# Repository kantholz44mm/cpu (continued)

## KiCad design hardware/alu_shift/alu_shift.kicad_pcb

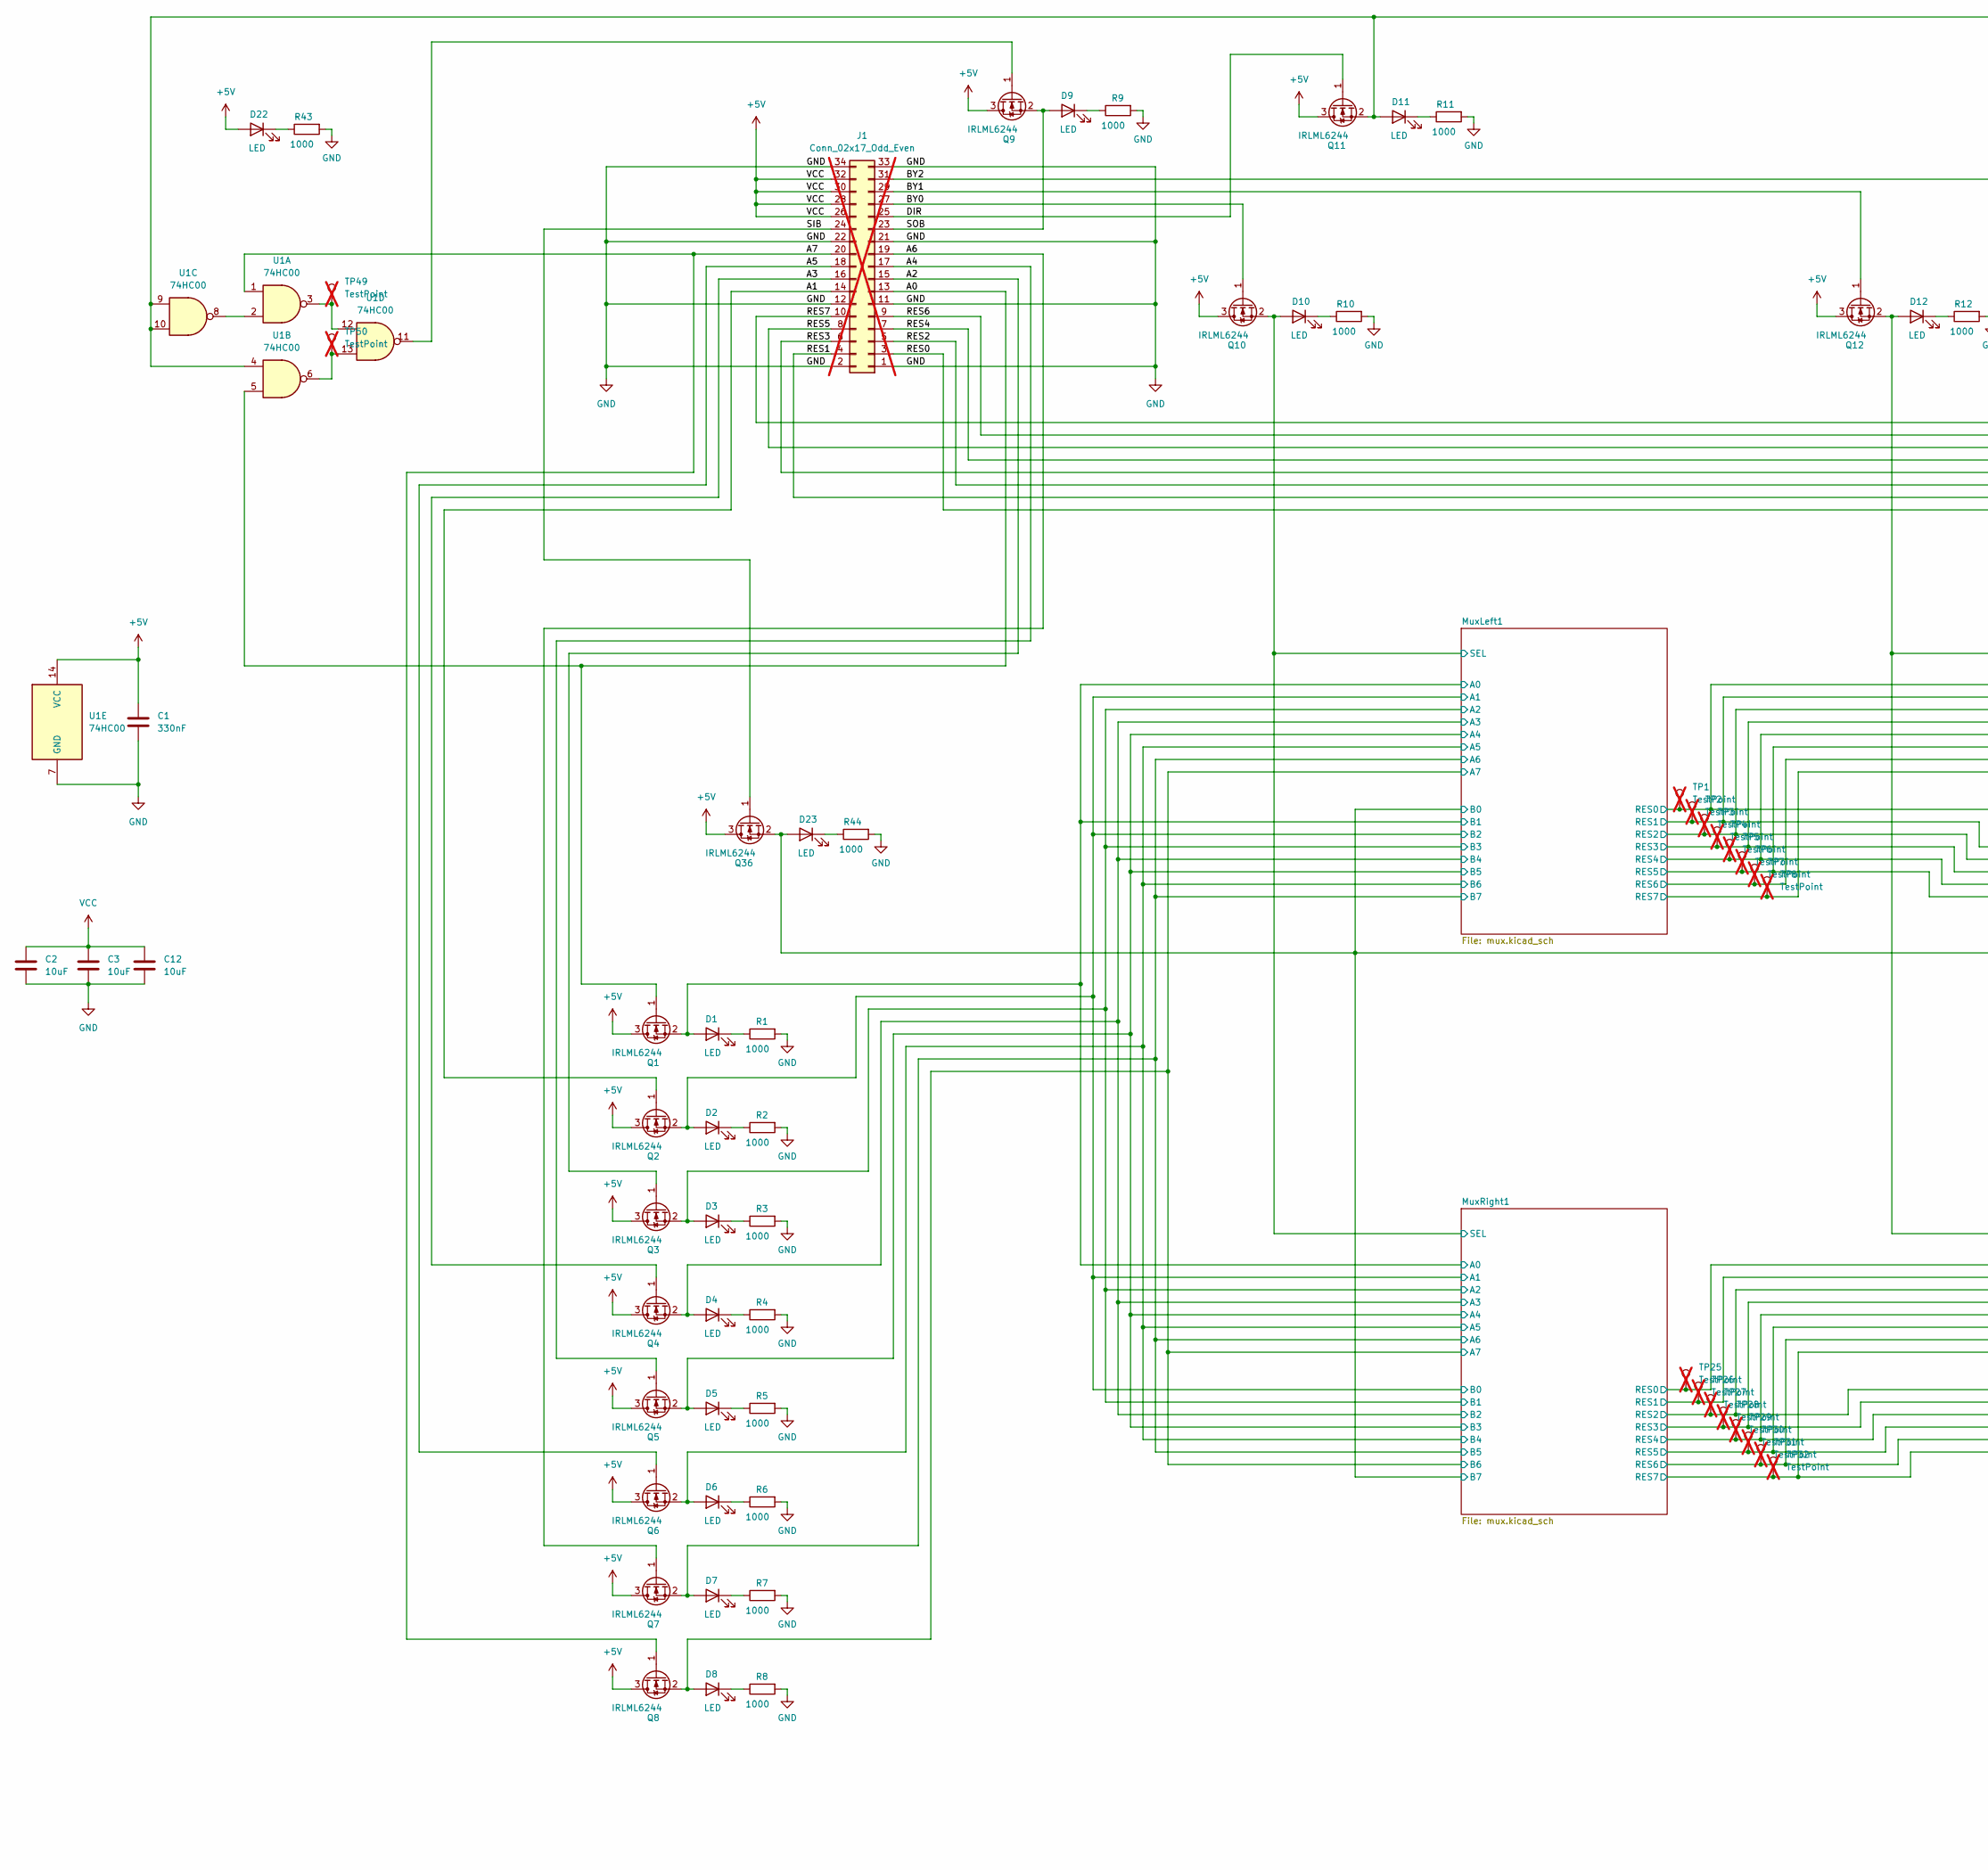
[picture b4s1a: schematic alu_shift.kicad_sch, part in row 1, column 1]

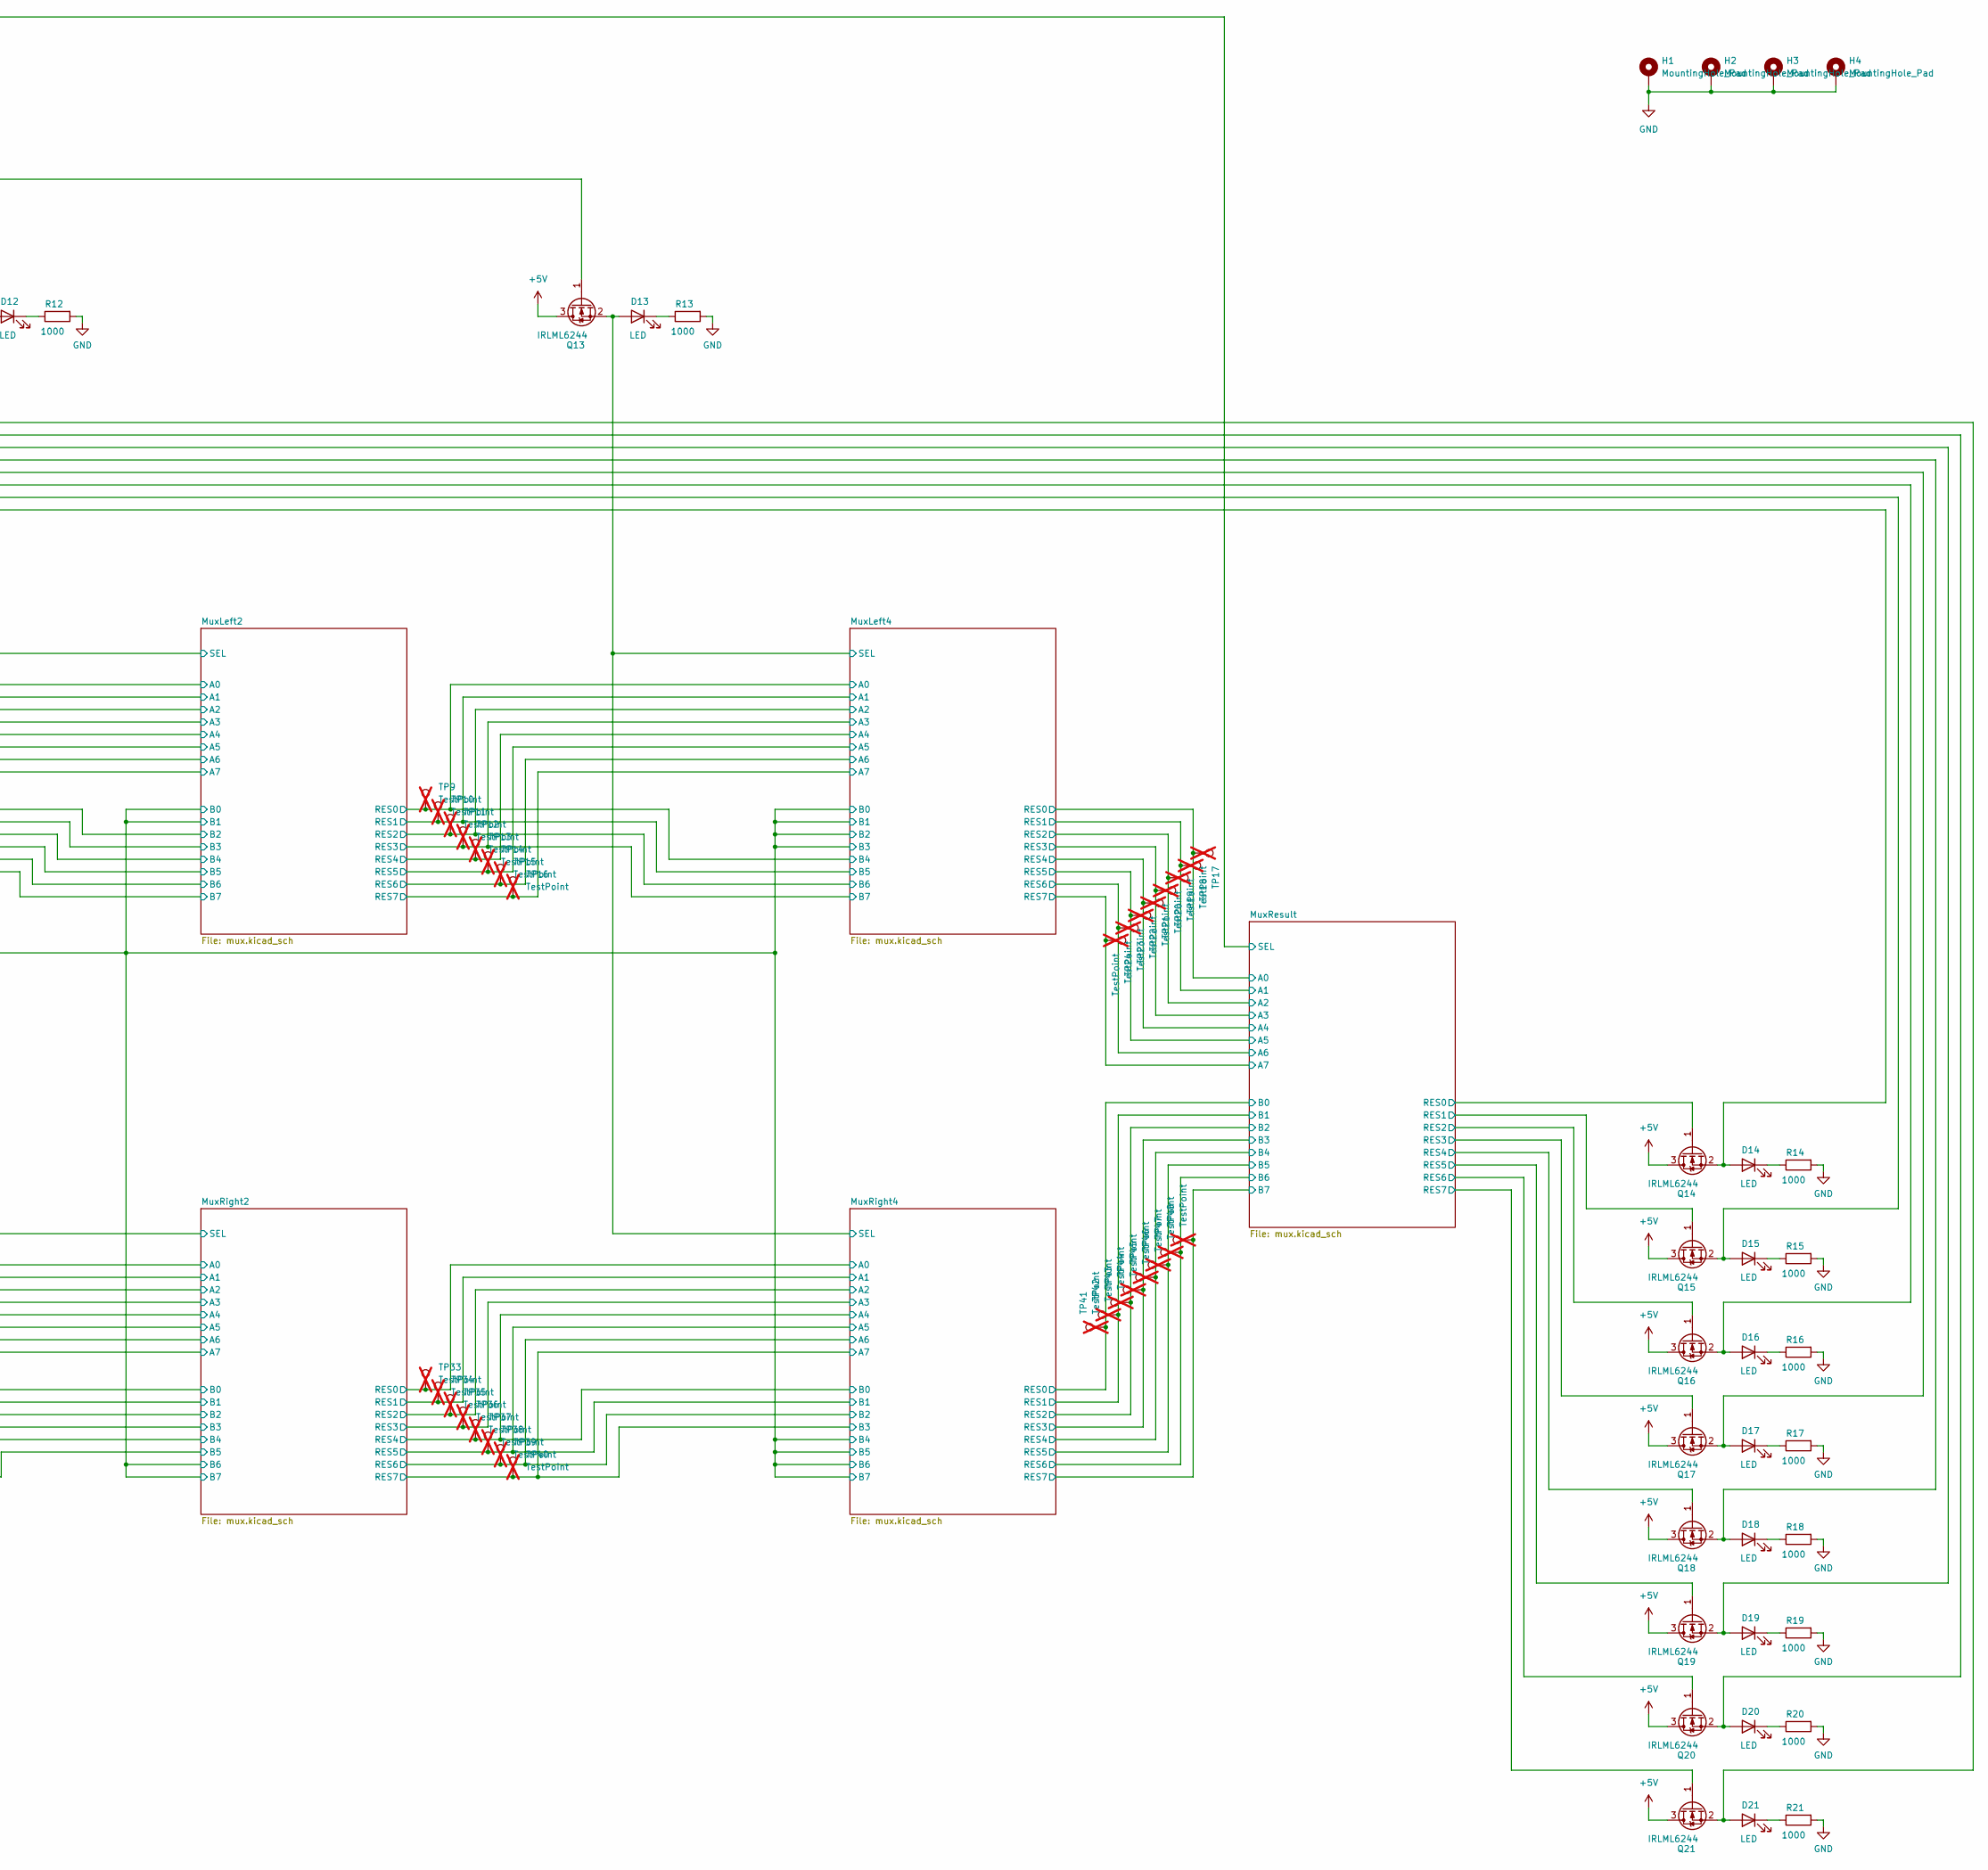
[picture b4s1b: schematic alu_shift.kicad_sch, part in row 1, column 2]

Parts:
C1: 330nF; C_0603_1608Metric_Pad1.08x0.95mm_HandSolder; LCSC C2918485
C2, C3, C12: 10uF; C_0603_1608Metric_Pad1.08x0.95mm_HandSolder; LCSC C2909630
D1, D2, D3, D4, D5, D6, D7, D8, D9, D10, D11, D12, D13, D14, D15, D16, D17, D18, D19, D20, D21, D22, D23: LED; LED_0603_1608Metric_Pad1.05x0.95mm_HandSolder; LCSC C84267
H1, H2, H3, H4: MountingHole_Pad; MountingHole_2.2mm_M2_Pad
J1: Conn_02x17_Odd_Even; PinHeader_2x17_P2.54mm_Horizontal; not fitted
Q1, Q2, Q3, Q4, Q5, Q6, Q7, Q8, Q9, Q10, Q11, Q12, Q13, Q14, Q15, Q16, Q17, Q18, Q19, Q20, Q21, Q36: IRLML6244; SOT-23-3; LCSC C5123965
R1, R2, R3, R4, R5, R6, R7, R8, R9, R10, R11, R12, R13, R14, R15, R16, R17, R18, R19, R20, R21, R43, R44: 1000; R_0603_1608Metric_Pad0.98x0.95mm_HandSolder; LCSC C21190
TP1, TP2, TP3, TP4, TP5, TP6, TP7, TP8, TP9, TP10, TP11, TP12, TP13, TP14, TP15, TP16, TP17, TP18, TP19, TP20, TP21, TP22, TP23, TP24, TP25, TP26, TP27, TP28, TP29, TP30, TP31, TP32, TP33, TP34, TP35, TP36, TP37, TP38, TP39, TP40, TP41, TP42, TP43, TP44, TP45, TP46, TP47, TP48, TP49, TP50: TestPoint; TestPoint_Pad_D2.0mm; not fitted
U1: 74HC00; SOIC-14_3.9x8.7mm_P1.27mm; LCSC C5586

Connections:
+5V: C1.1, C2.1, C3.1, C12.1, D22.2 (A), J1.26, J1.28, J1.30, J1.32, Q1.3 (D), Q2.3 (D), Q3.3 (D), Q4.3 (D), Q5.3 (D), Q6.3 (D), Q7.3 (D), Q8.3 (D), Q9.3 (D), Q10.3 (D), Q11.3 (D), Q12.3 (D), Q13.3 (D), Q14.3 (D), Q15.3 (D), Q16.3 (D), Q17.3 (D), Q18.3 (D), Q19.3 (D), Q20.3 (D), Q21.3 (D), Q36.3 (D), U1.14 (VCC); also elsewhere on the board
/A0: J1.13, Q1.1 (G), U1.5
/A1: J1.14, Q2.1 (G)
/A2: J1.15, Q3.1 (G)
/A3: J1.16, Q4.1 (G)
/A4: J1.17, Q5.1 (G)
/A5: J1.18, Q6.1 (G)
/A6: J1.19, Q7.1 (G)
/A7: J1.20, Q8.1 (G), U1.1
/BY0: J1.27, Q10.1 (G)
/BY1: J1.29, Q12.1 (G)
/BY2: J1.31, Q13.1 (G)
/DIR: J1.25, Q11.1 (G)
/MuxLeft1/A0: D1.2 (A), Q1.2 (S); also elsewhere on the board
/MuxLeft1/A1: D2.2 (A), Q2.2 (S); also elsewhere on the board
/MuxLeft1/A2: D3.2 (A), Q3.2 (S); also elsewhere on the board
/MuxLeft1/A3: D4.2 (A), Q4.2 (S); also elsewhere on the board
/MuxLeft1/A4: D5.2 (A), Q5.2 (S); also elsewhere on the board
/MuxLeft1/A5: D6.2 (A), Q6.2 (S); also elsewhere on the board
/MuxLeft1/A6: D7.2 (A), Q7.2 (S); also elsewhere on the board
/MuxLeft1/A7: D8.2 (A), Q8.2 (S); also elsewhere on the board
/MuxLeft1/B0: D23.2 (A), Q36.2 (S); also elsewhere on the board
/MuxLeft1/RES0: TP1.1; also elsewhere on the board
/MuxLeft1/RES1: TP2.1; also elsewhere on the board
/MuxLeft1/RES2: TP3.1; also elsewhere on the board
/MuxLeft1/RES3: TP4.1; also elsewhere on the board
/MuxLeft1/RES4: TP5.1; also elsewhere on the board
/MuxLeft1/RES5: TP6.1; also elsewhere on the board
/MuxLeft1/RES6: TP7.1; also elsewhere on the board
/MuxLeft1/RES7: TP8.1; also elsewhere on the board
/MuxLeft1/SEL: D10.2 (A), Q10.2 (S); also elsewhere on the board
/MuxLeft2/RES0: TP9.1; also elsewhere on the board
/MuxLeft2/RES1: TP10.1; also elsewhere on the board
/MuxLeft2/RES2: TP11.1; also elsewhere on the board
/MuxLeft2/RES3: TP12.1; also elsewhere on the board
/MuxLeft2/RES4: TP13.1; also elsewhere on the board
/MuxLeft2/RES5: TP14.1; also elsewhere on the board
/MuxLeft2/RES6: TP15.1; also elsewhere on the board
/MuxLeft2/RES7: TP16.1; also elsewhere on the board
/MuxLeft2/SEL: D12.2 (A), Q12.2 (S); also elsewhere on the board
/MuxLeft4/RES0: TP17.1; also elsewhere on the board
/MuxLeft4/RES1: TP18.1; also elsewhere on the board
/MuxLeft4/RES2: TP19.1; also elsewhere on the board
/MuxLeft4/RES3: TP20.1; also elsewhere on the board
/MuxLeft4/RES4: TP21.1; also elsewhere on the board
/MuxLeft4/RES5: TP22.1; also elsewhere on the board
/MuxLeft4/RES6: TP23.1; also elsewhere on the board
/MuxLeft4/RES7: TP24.1; also elsewhere on the board
/MuxLeft4/SEL: D13.2 (A), Q13.2 (S); also elsewhere on the board
/MuxResult/B0: TP41.1; also elsewhere on the board
/MuxResult/B1: TP42.1; also elsewhere on the board
/MuxResult/B2: TP43.1; also elsewhere on the board
/MuxResult/B3: TP44.1; also elsewhere on the board
/MuxResult/B4: TP45.1; also elsewhere on the board
/MuxResult/B5: TP46.1; also elsewhere on the board
/MuxResult/B6: TP47.1; also elsewhere on the board
/MuxResult/B7: TP48.1; also elsewhere on the board
/MuxResult/RES0: Q14.1 (G); also elsewhere on the board
/MuxResult/RES1: Q15.1 (G); also elsewhere on the board
/MuxResult/RES2: Q16.1 (G); also elsewhere on the board
/MuxResult/RES3: Q17.1 (G); also elsewhere on the board
/MuxResult/RES4: Q18.1 (G); also elsewhere on the board
/MuxResult/RES5: Q19.1 (G); also elsewhere on the board
/MuxResult/RES6: Q20.1 (G); also elsewhere on the board
/MuxResult/RES7: Q21.1 (G); also elsewhere on the board
/MuxResult/SEL: D11.2 (A), Q11.2 (S), U1.4, U1.9, U1.10; also elsewhere on the board
/MuxRight1/RES0: TP25.1; also elsewhere on the board
/MuxRight1/RES1: TP26.1; also elsewhere on the board
/MuxRight1/RES2: TP27.1; also elsewhere on the board
/MuxRight1/RES3: TP28.1; also elsewhere on the board
/MuxRight1/RES4: TP29.1; also elsewhere on the board
/MuxRight1/RES5: TP30.1; also elsewhere on the board
/MuxRight1/RES6: TP31.1; also elsewhere on the board
/MuxRight1/RES7: TP32.1; also elsewhere on the board
/MuxRight2/RES0: TP33.1; also elsewhere on the board
/MuxRight2/RES1: TP34.1; also elsewhere on the board
/MuxRight2/RES2: TP35.1; also elsewhere on the board
/MuxRight2/RES3: TP36.1; also elsewhere on the board
/MuxRight2/RES4: TP37.1; also elsewhere on the board
/MuxRight2/RES5: TP38.1; also elsewhere on the board
/MuxRight2/RES6: TP39.1; also elsewhere on the board
/MuxRight2/RES7: TP40.1; also elsewhere on the board
/RES0: D14.2 (A), J1.3, Q14.2 (S)
/RES1: D15.2 (A), J1.4, Q15.2 (S)
/RES2: D16.2 (A), J1.5, Q16.2 (S)
/RES3: D17.2 (A), J1.6, Q17.2 (S)
/RES4: D18.2 (A), J1.7, Q18.2 (S)
/RES5: D19.2 (A), J1.8, Q19.2 (S)
/RES6: D20.2 (A), J1.9, Q20.2 (S)
/RES7: D21.2 (A), J1.10, Q21.2 (S)
/SIB: J1.24, Q36.1 (G)
/SOB: D9.2 (A), J1.23, Q9.2 (S)
GND: C1.2, C2.2, C3.2, C12.2, H1.1, H2.1, H3.1, H4.1, J1.1, J1.2, J1.11, J1.12, J1.21, J1.22, J1.33, J1.34, R1.2, R2.2, R3.2, R4.2, R5.2, R6.2, R7.2, R8.2, R9.2, R10.2, R11.2, R12.2, R13.2, R14.2, R15.2, R16.2, R17.2, R18.2, R19.2, R20.2, R21.2, R43.2, R44.2, U1.7 (GND); also elsewhere on the board
unnamed: D1.1 (K), R1.1
unnamed: D2.1 (K), R2.1
unnamed: D3.1 (K), R3.1
unnamed: D4.1 (K), R4.1
unnamed: D5.1 (K), R5.1
unnamed: D6.1 (K), R6.1
unnamed: D7.1 (K), R7.1
unnamed: D8.1 (K), R8.1
unnamed: D9.1 (K), R9.1
unnamed: D10.1 (K), R10.1
unnamed: D11.1 (K), R11.1
unnamed: D12.1 (K), R12.1
unnamed: D13.1 (K), R13.1
unnamed: D14.1 (K), R14.1
unnamed: D15.1 (K), R15.1
unnamed: D16.1 (K), R16.1
unnamed: D17.1 (K), R17.1
unnamed: D18.1 (K), R18.1
unnamed: D19.1 (K), R19.1
unnamed: D20.1 (K), R20.1
unnamed: D21.1 (K), R21.1
unnamed: D22.1 (K), R43.1
unnamed: D23.1 (K), R44.1
unnamed: Q9.1 (G), U1.11
unnamed: TP49.1, U1.3, U1.12
unnamed: TP50.1, U1.6, U1.13
unnamed: U1.2, U1.8
